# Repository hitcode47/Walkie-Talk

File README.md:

# 📡 Walkie-Talk
 - Este modelo de rádio comunicador faz parte da proposta de projeto calouros e visa o enriquecimento e melhoria do acervo no âmbito da iniciativa PETEE Protótipos (UFMG). Como proposta inicial, será desenvolvido um protótipo voltado à experimentação em Telecomunicações, aplicável em disciplinas e oficinas de extensão. O modelo consiste em um protótipo de circuitos gêmeos, criados aos pares ou mais, em cada um deles, além dos periféricos de comunicação, haverá um módulo transceptor que, quando operando na mesma frequência, será capaz de manter um canal de comunicação.
---

## 📌 Objetivo do protótipo e documentação
- Demonstrar um modocumentação **didática, funcional, completa e de fácil edição**.
- Demonstra a importância em separar dodumentação e relatório.
- Produzir um protótipo acessível para estudantes e que diversifique o acervo do Petee.
- Apoiar atividades de ensino e extensão com um material prático e interativo.

---
## ⚡ Especificações – Módulo SA828-U  

| Categoria                     | Especificação |
|-------------------------------|---------------|
| **Faixa de frequência (UHF)** | 400 – 480 MHz |
| **Potência de saída (TX)**    | até ~1.5 W (≈ 30 a 32.5 dBm) |
| **Sensibilidade (RX)**        | ~–124 dBm |
| **Alcance estimado**          | 3 – 5 km em campo aberto (dependendo da antena e ambiente) |
| **Alimentação (Vcc)**         | 3.3 V a 5.5 V (típico 4.2 V) |

### Consumo de Corrente  

| Modo                  | Corrente típica |
|------------------------|-----------------|
| RX                     | ~60 mA |
| TX (alta potência)     | ~800 – 900 mA |
| TX (baixa potência)    | ~350 – 450 mA |
| Repouso (sleep)        | ≤ 3 µA |

### Comunicação  

| Parâmetro                  | Especificação |
|-----------------------------|---------------|
| Largura de banda            | 12.5 kHz / 25 kHz |
| Modulação                   | FM |
| Rejeição de canal adjacente | –60 dBc a 12.5 kHz |
| Códigos de áudio            | CTCSS (38 níveis), CDCSS (166 níveis) |

### Áudio  

| Parâmetro                  | Especificação |
|-----------------------------|---------------|
| Saída do alto-falante       | ~2 W |
| Impedância recomendada       | 8 Ω |

### Recursos Extras
- Controle de potência (alto/baixo) via pino H/L  
- Configuração via interface UART e software de PC  
- Oscilador TCXO 1 ppm (alta estabilidade de frequência)  
- Temperatura de operação: –30 °C a +70 °C  

---

## 🧰 Materiais Usados
| Referência | Quantidade | Valor / Modelo | Descrição                             | Datasheet                                                   |
| ---------- | ---------- | -------------- | ------------------------------------- | ----------------------------------------------------------- |
| BT1        | 1          | 1042           | Suporte de bateria                    | [PDF](https://www.diodes.com/assets/Datasheets/ds30396.pdf) |
| D1         | 1          | 1N4148WT       | Diodo retificador rápido, 75V / 0.15A | [PDF](https://www.diodes.com/assets/Datasheets/ds30396.pdf) |
| LS1        | 1          | POM-3542P-R    | Microfone eletreto                    | [PDF](https://www.diodes.com/assets/Datasheets/ds30396.pdf) |
| LS2        | 1          | KSSG2308       | Alto-falante                          | [PDF](https://www.diodes.com/assets/Datasheets/ds30396.pdf) |
| S1         | 1          | PB400OAQR1BLK  | Botão push-button                     | [PDF](https://www.diodes.com/assets/Datasheets/ds30396.pdf) |
| SATRX1     | 1          | SA828U         | Módulo de rádio UHF                   | [PDF](https://www.diodes.com/assets/Datasheets/ds30396.pdf) |

---

## 📐 Esquemáticos
- **Esquemático**  

- **Footprint**  

---
## 🖼️ Modelos 3D  

- 📂 [Arquivos de carcaça e suporte (STL/STEP)](./3d_models)  

### PCB  

- **Modelo Frontal**  

- **Modelo de Fundo**  

---

## 🎥 Mídia    

- **Vídeo 1 – Visão PCB**  

- **Vídeo 2 – Visão Compacta**  

- **Vídeo 3 – Visão Explodida**  

---

## 🛠️ Processo de Produção (Ainda em construção)
1. **Definição de requisitos** (alcance, custo, alimentação).  
2. **Projeto esquemático** no KiCad.  
3. **Protótipo em breadboard** para testes iniciais.  
4. **PCB** e montagem final.  
5. **Testes de calibração e validação**.  
6. **Documentação e publicação** no GitHub.  

---

## 📚 Referências
- Sedra & Smith – *Microeletrônica*.  
- Haykin – *Sistemas de Comunicação*.  
- Tutoriais de RF (AllAboutCircuits, EEVBlog).  
- Documentação interna PETEE.  

---

## 👥 Equipe
- **PETEE – UFMG**  
- Petiano responsável: *[Bruno dos Santos Lopes]*  
- Tutor: *[Nome do Professor]*  

---

## 📢 Licença
Projeto aberto para fins didáticos. Cite **PETEE – UFMG** ao utilizar.  

---

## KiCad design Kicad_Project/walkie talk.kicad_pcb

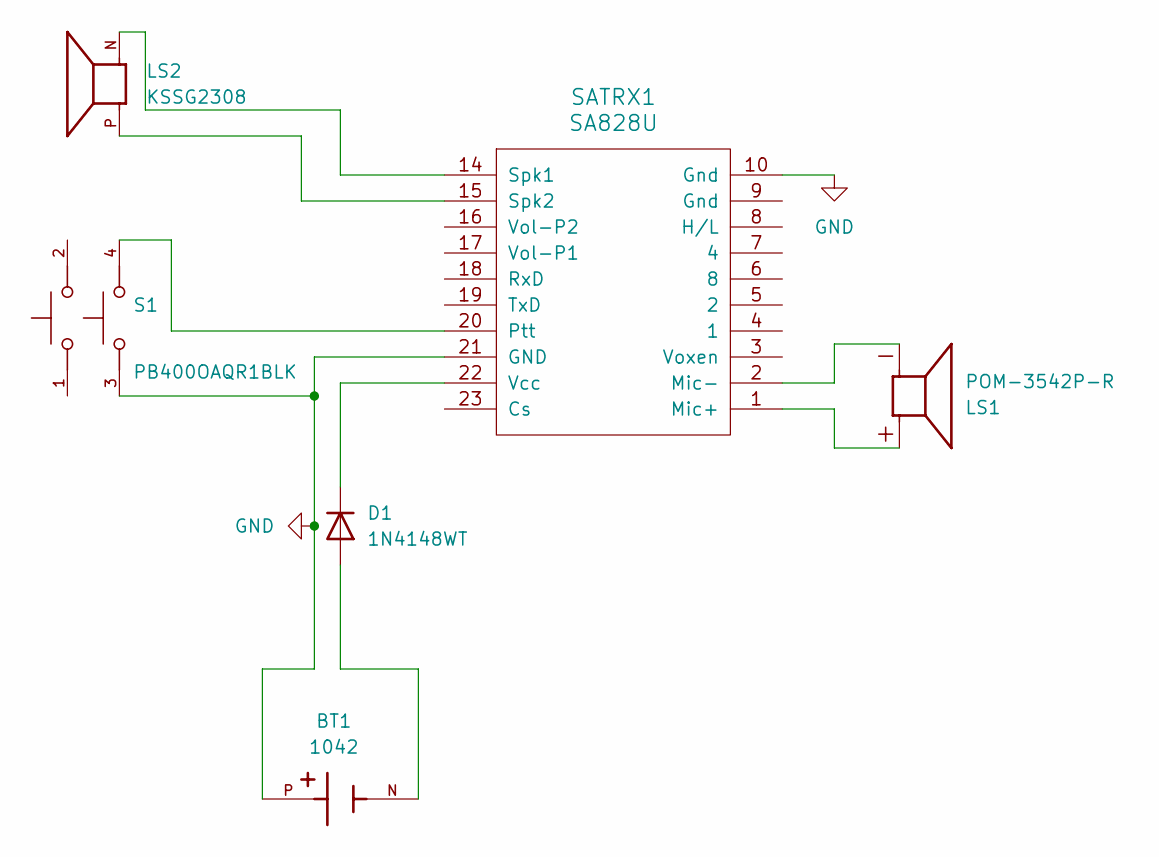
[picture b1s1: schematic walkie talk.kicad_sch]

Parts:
BT1: 1042; BAT_1042; PARTREV E
D1: 1N4148WT; D_SOD-523
LS1: POM-3542P-R; MIC_POM-3542P-R; PARTREV B
LS2: KSSG2308; SPKR_KSSG2308; PARTREV 1.3
S1: PB400OAQR1BLK; SW_PB400OAQR1BLK; PARTREV A
SATRX1: SA828U

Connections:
GND: BT1.P, S1.3, SATRX1.10 (Gnd), SATRX1.21 (GND)
unnamed: BT1.N, D1.2 (A)
unnamed: D1.1 (K), SATRX1.22 (Vcc)
unnamed: LS1.P, SATRX1.1 (Mic+)
unnamed: LS1.N, SATRX1.2 (Mic-)
unnamed: S1.4, SATRX1.20 (Ptt)
unnamed: LS2.N, SATRX1.14 (Spk1)
unnamed: LS2.P, SATRX1.15 (Spk2)

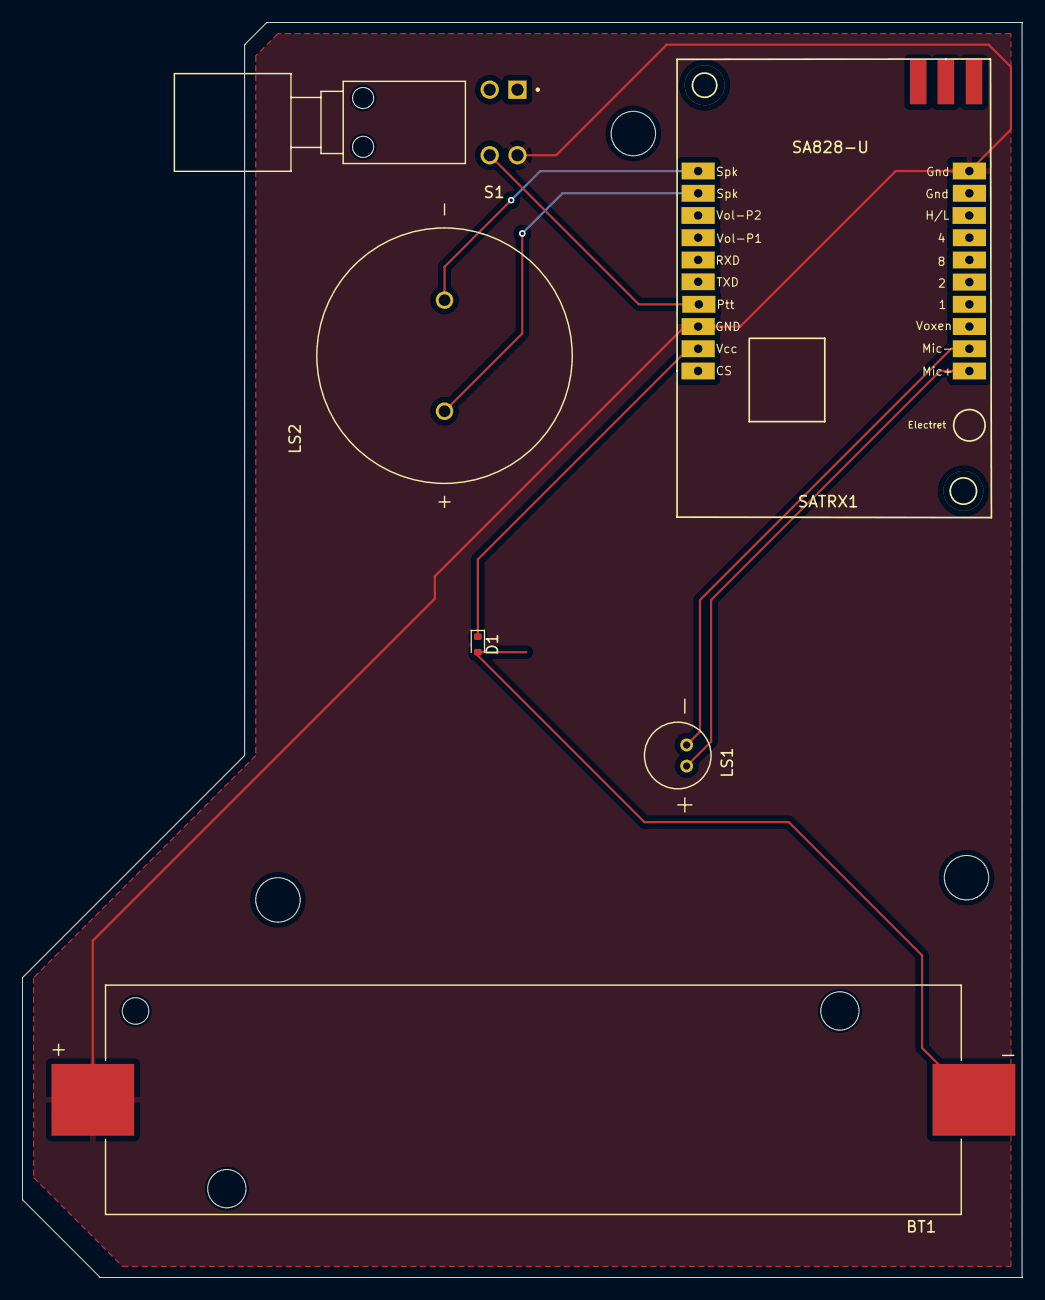
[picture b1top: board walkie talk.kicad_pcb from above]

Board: 2 copper layers, 90.0 x 113.0 mm, 6 parts (0 on the bottom side), 8 nets.

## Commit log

2025-09-25 Update README.md
    Atualização 1 - Primeira descrição completa do readme
2025-09-26 Create readme
    Descrição sobre imagens
2025-09-26 Create readme
    repositório de vídeos
2025-09-26 Create Arquivos_3D
2025-09-26 Rename readme to readme.md
2025-09-26 Rename readme.md to readme.md
2025-11-11 Update README with enhanced project description
    Revised project description for clarity and detail.
2025-11-11 Fix formatting in README.md
2025-11-11 Fix formatting issues in README.md
2025-11-11 Fix wording in README.md description
2025-11-11 Fix typo in README description
